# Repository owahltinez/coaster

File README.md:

# Coaster

Very simple battery-operated device. When you push a button, the light turns on for a few seconds
and then it turns off. It is designed to be used as a coaster such that, when gently pushing a glass
down on the device, the light activates making the contents of the glass glow.

Pressing down on the coaster triggers a ~8 second light show: the LEDs ramp up to full
brightness, "breathe" gently five times, and fade back to black. Between shows the device
sleeps at ~1 µA — there is no on/off switch and none is needed.

## Repository layout

- `firmware/` — AVR C firmware and its build/flash Makefile.
- `pcb/` — v0.3 board design (KiCad, generated from python scripts) and footprints.
- `enclosure/` — 3D-printed shell (FreeCAD source + STEP/STL export).
- `tools/` — pinned toolchain containers (KiCad for the board, avr-gcc for the firmware).

All subdirectories share the same verbs, and the top-level Makefile forwards to each:
`make build` (firmware hex + board + enclosure exports), `make test` (flash-fit check +
board DRC + enclosure solidity check), `make clean`. Domain-specific verbs forward to the
relevant subdirectory: `make flash` / `make fuses` (firmware programming),
`make review` (board render / PDF / STEP), `make fab` (JLCPCB order bundle). The
firmware and PCB verbs run inside pinned containers — `make image` builds them once
(see Software); flashing stays on the host.

## How it works

The button connects an MCU pin (with its internal pull-up) to ground. Pressing it fires a
falling-edge interrupt on one of the ATtiny202's fully-asynchronous pins, which wakes the
chip from power-down sleep with the main clock stopped — a press costs effectively no
charge. The firmware debounces the edge, plays the show over hardware PWM through a
MOSFET driving four series-resistored LEDs, and goes back to sleep.

Two details carry hard-won lessons from v0.2:

- The show also plays once when the battery is inserted (a power-on reset doubles as a
  built-in self test), but *only* on a power-on reset: a brown-out reset means a dying
  cell sagged below 1.8V mid-show, and playing again would loop the cell to death — so a
  brown-out goes straight back to sleep and the coaster simply dims gracefully as the
  battery wears out.
- Wake edges that turn out not to be presses (e.g. contact bounce while lifting a glass
  off a held-down button) are filtered by a 20ms debounce check, so the show plays on
  deliberate presses only.

## Hardware

The v0.3 design (KiCad) lives in `pcb/`:

- `pcb/design.py` is the circuit as data — parts, placements, and the netlist defined
  once. This is the file to read or edit; it is the source of truth.
- `pcb/DESIGN.md` is the design specification: pin map, BOM with part rationale,
  ordering plan, and the validation checklists.
- `pcb/generate.py` turns `design.py` into `coaster.kicad_pcb` (committed for
  convenience). `make build` regenerates the board and validates connectivity; `make
  test` runs DRC; `make review` produces a board render, a 1:1 printable PDF, and a STEP
  model for CAD fit checks.
- `pcb/coaster.pretty/` — project footprints with pad geometry extracted from the
  manufactured v0.2 board (battery holder, tactile switch).

There is no schematic: JLCPCB takes Gerbers + BOM + CPL (not a schematic), the board is
built and checked directly against `design.py`, and `design.py` itself documents the
circuit — so a derived schematic would add nothing.

The previous revision (v0.2: ATtiny13A, EasyEDA, CR2032) is archived at release
[v0.2.1](https://github.com/owahltinez/coaster/releases/tag/v0.2.1), including its
firmware, schematic renderings, and 3D printing assets.

### Production

All SMD parts are LCSC-stocked, so the board can be fabricated and assembled through
JLCPCB — the only hand-assembly per unit is dropping a CR2016 into the holder. `make
fab` writes the three JLCPCB uploads (Gerbers zip + BOM + CPL) to `pcb/dist/`; order
with **white soldermask** (the board face is the reflector behind the LEDs). The full
step-by-step — orientation checks, stock confirmation, post-assembly flashing — is the
ordering plan in [pcb/DESIGN.md](pcb/DESIGN.md).

Rough per-unit estimates as of June 2026 (USD, assembled and shipped; ~A$1.55/US$):

| Per unit               | Qty 30  | Qty 100 | Qty 1k  | Qty 10k |
|------------------------|---------|---------|---------|---------|
| Parts                  | $0.74   | $0.70   | ~$0.60  | ~$0.47  |
| Feeder/setup/stencil   | $0.72   | $0.30   | ~$0.04  | ~$0     |
| PCB + assembly         | $0.47   | $0.40   | ~$0.30  | ~$0.20  |
| Board shipping         | $0.20   | $0.35   | ~$0.10  | ~$0.05  |
| CR2016 (name-brand)    | $0.65   | $0.35   | ~$0.20  | ~$0.12  |
| Enclosure              | $0.60 (FDM) | $0.60 (FDM) | ~$1.00 (print farm)\* | ~$0.30 (molded)\* |
| **Finished coaster**   | **~$3.40** | **~$2.70** | **~$2.25** | **~$1.10** |

\*The 1k column keeps FDM but prices it honestly: ~2,500 printer-hours, which a small
farm of four budget printers clears in under a month — filament plus printer
amortization lands near $1/unit, with no tooling commitment and the printers kept at
the end. The 10k column switches to injection molding (aluminum tooling, amortized);
that is also the column where a further redesign pays — shrinking the PCB from the
structural 50×50mm to a ~25mm puck and letting the molded shell carry the mechanical
roles would cut the PCB line by ~$0.10 more. If 1k is a milestone toward 10k rather
than the destination, rapid aluminum tooling (~$1–1.5k) prices similarly at 1k and
carries forward.

The electronics architecture is the same in every column — the MCU ($0.30–0.43) is the
cheapest line that matters, and it is the entire personality of the product. Prices
drift; get a real quote from the [JLCPCB quote tool](https://jlcpcb.com/quote) and
confirm ATtiny202 stock at order time (the ATtiny402 is a firmware-compatible drop-in
substitute).

## Software

The firmware and board builds run in **pinned containers** (`tools/`), so the host
needs neither a KiCad nor an AVR toolchain — only a container engine. Pinning is what
keeps the artifacts reproducible: the committed board is KiCad-10 format and host KiCad
drifts (Debian ships v9, which can't even open a v10 board), and the ATtiny202 firmware
needs avr-gcc ≥ 12 (the README used to hand-source `avr-gcc@14` from the
[osx-cross/avr](https://github.com/osx-cross/homebrew-avr) tap on macOS). Build the
images once, then the verbs route through them automatically:

```bash
make image               # build both images: coaster-fw + coaster-pcb (re-run after editing a Containerfile)
make build               # firmware hex + board + enclosure, each in its toolchain
make fab                 # regenerate the board + emit the JLCPCB bundle, in the container
```

The enclosure builds the same way, in a pinned FreeCAD 1.1.1 container (`make image`
builds it too) — so the host needs no FreeCAD either, and the old macOS `freecadcmd`
symlink dance is gone.

`docker` here is a [Podman](https://podman.io) alias (`podman-docker`); override
`CONTAINER_ENGINE` to use another runtime. Rootless Podman maps container-root to your
UID (the Makefile passes `--user 0`), so generated files come back owned by you. The
rule is **produce artifacts in a container, touch hardware on the host** — so flashing
(`make flash` / `make fuses`, which need a USB-serial adapter) stays on the host and
needs `avrdude` (≥ 7, for `serialupdi`) installed there; see Flashing below.

The **enclosure** build still runs on the host via FreeCAD (`freecadcmd`); on macOS the
app bundle doesn't expose its CLI, so symlink it once:

```bash
ln -s /Applications/FreeCAD.app/Contents/Resources/bin/freecadcmd /opt/homebrew/bin/freecadcmd
```

### Flashing

No dedicated programmer needed: UPDI works over any USB-serial adapter with a single
~1kΩ resistor bridging the adapter's TX to RX, and RX wired to the board's UPDI pad
(plus VDD and GND — the J1 pads are labeled on the silkscreen).

```bash
make flash   # writes main.hex over serialupdi
make fuses   # once per chip: brown-out detector at 1.8V, sampled in sleep
```

The fuses matter: the factory default leaves the BOD disabled, which allows undefined
behavior when the battery sags, and the firmware's brown-out logic depends on it.

For flashing a stack of boards hands-free, `make flash-loop` runs a continuous loop:
plug a board onto the jig, it flashes + fuses + verifies automatically, then waits for
you to remove it before arming the next. **The board reports its own result** — a good
flash plays a distinct rapid blink and a failed one stays dark, so you never look at the
screen. The blink is gated on a one-shot EEPROM flag the loop writes only after both
flash and fuses verify (a single avrdude run, which aborts before the arm step on any
earlier failure); the firmware blinks once on the next boot and clears the flag, so it
fires exactly once per flash and never again in the field.

Gotchas:

- **Remove the coin cell before flashing.** The adapter drives VDD and would back-feed
  the (non-rechargeable) lithium cell.
- That's it. The v0.2 list of ISP gotchas (LEDs clamping MOSI, flaky readback, wedged
  programmers) died with the ISP header: UPDI shares no pins with anything else on this
  board, by construction.

## Power estimates

Assumptions: CR2016 rated at 75 mAh (~70 mAh usable), ~8 mA LED draw at 100% duty on a
fresh cell, ~1 µA sleep current (BOD sampled).

| Event                  | Cost     | Notes                                          |
|------------------------|----------|------------------------------------------------|
| Light show (~8 s)      | ~15 µAh  | avg ~60% LED duty + ~1.5 mA MCU active         |
| Button press           | ~0       | pin-change wake; nothing touches the supply    |
| Standby (per day)      | ~26 µAh  | ~1 µA sleep + battery self-discharge           |

Expected battery life:

| Usage pattern               | Battery life      |
|-----------------------------|-------------------|
| Never pressed (shelf)       | ~7 years          |
| ~5 presses/day              | ~2 years          |
| ~30 presses/day (bar duty)  | ~5 months         |
| Theoretical max shows       | ~4,500            |

The punchline: v0.3 runs on a cell with a third of the v0.2 battery's capacity and
still matches its life, because presses are now free (each v0.2 press dead-shorted the
battery and cost as much as a show) and sleep current dropped ~4×.

## Demo

> TODO: Add demo pictures / video.

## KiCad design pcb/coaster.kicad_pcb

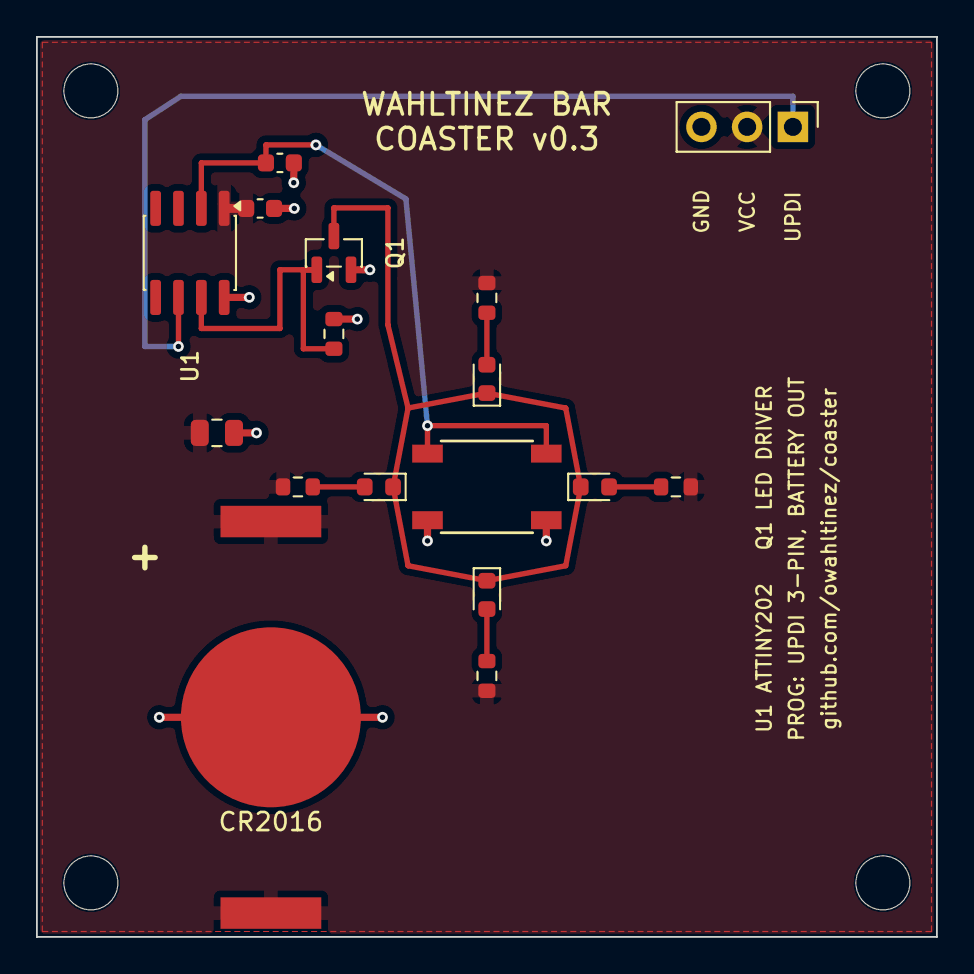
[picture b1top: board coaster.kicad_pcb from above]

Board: 2 copper layers, 50.0 x 50.0 mm, 21 parts (0 on the bottom side), 10 nets.

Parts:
BT1: CR2016; MY-2016-02
C1, C3: 100nF; C_0603_1608Metric
C2: 22uF; C_0805_2012Metric
H1, H2, H3, H4: 3mm; MountingHole_3mm
J1: UPDI; PinHeader_1x03_P2.54mm_Vertical
L1, L2, L3, L4: KT-0603W; LED_0603_1608Metric
Q1: AO3400A; SOT-23
R1, R2, R3, R4: 100; R_0603_1608Metric
R5: 100k; R_0603_1608Metric
SW1: TS-1187A-B-A-B; TS-1187A
U1: ATtiny202-SSN; SOIC-8_3.9x4.9mm_P1.27mm

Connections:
BUTTON: C3.1, SW1.1, U1.2
GND: BT1.2, C1.2, C2.2, C3.2, J1.3, Q1.2, R5.2, SW1.2, U1.8
LED_A1: L1.2, R1.2
LED_A2: L2.2, R2.2
LED_A3: L3.2, R3.2
LED_A4: L4.2, R4.2
LED_K: L1.1, L2.1, L3.1, L4.1, Q1.3
LED_PWM: Q1.1, R5.1, U1.7
UPDI: J1.1, U1.6
VCC: BT1.1, C1.1, C2.1, J1.2, R1.1, R2.1, R3.1, R4.1, U1.1

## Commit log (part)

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2024-06-26 Update BOM with SMD parts
2024-08-01 Pulse LED using PWM
2024-08-17 Simplify LED routine
2026-06-06 Make flashing reliable over a hand-held ISP cable
    Fix the install target (usbasp uses -P usb, no baud rate; drop -F)
    and tune it for this board's quirks: the LEDs hang on the MOSI line,
    so writes silently truncate at higher ISP clocks while reads stay
    reliable (data returns on the unloaded MISO line). Write at 32kHz
    without inline verification, then verify in a separate pass at
    16kHz. Add a fuses target for the one-time BOD setup and a reset
2026-06-06 Fix reset-relight loop and add breathing glow effect
    A worn CR2032 sagging under LED load could brown out the MCU
    mid-show; since a reboot unconditionally replayed the show, the
    device got stuck relighting forever. Three layers of fixes:
    - Enable BOD at 1.8V awake (requires hfuse=0xFD) so low-voltage
    operation resets cleanly instead of executing undefined behavior,
    and disable it during sleep via BODCR (the BODS bits are not in
2026-06-06 Document hardware: design files, BOM, flashing, power estimates
    Add the design files (Protel netlist as the canonical machine-readable
    circuit description, schematic SVG for humans, EasyEDA source for
    editing) and rewrite the README: how the device works, flashing
    recipe with fuse settings and hard-won gotchas, BOM matching the SMD
    parts actually on the board (with verified sources and pricing),
    JLCPCB production cost estimates, power budget and battery life
2026-06-08 Add v0.3 KiCad hardware design, generated and verified
    Reorganize the repo into three domain folders, each with a
    self-contained Makefile, plus a top-level Makefile that forwards to
    them (make install / board / review / clean):
    firmware/ AVR C firmware and its build/flash Makefile
    pcb/ v0.3 board design + generator + footprints
    enclosure/ 3D-printed shell (design constraints; CAD source TODO)
2026-06-09 Fix long-press brown-out and simplify show-on-press logic
    Two related fixes to the wake-and-play behavior, both rooted in the
    v0.2 button dead-shorting the battery to power-cycle the MCU:
    - Replace the .noinit SRAM cookie with the MCUSR PORF reset flag to
    decide whether to play the show. The cookie distinguished a button
    press from a mid-show brown-out by whether SRAM survived, which is
    timing-dependent and differed between short and long presses --
2026-06-09 Make board regeneration deterministic
    Every KiCad board item gets a random UUID at construction and KiCad
    serializes items in UUID order, so each generate.py run rewrote every
    UUID and reshuffled the file -- a ~4000-line no-op diff on regeneration.
    Seed KiCad's UUID generator (pcbnew.KIID.SeedGenerator) with a fixed
    value before building; with the script's fixed build order this makes
    the UUID sequence, and thus the whole file, byte-stable across runs.
2026-06-09 Switch battery to CR2016 (MY-2016-02) to slim the enclosure
    The battery holder was the tallest component, sitting just above the
    button. Swap the CR2032 holder (MY-2032-12, 3.6mm tall) for a CR2016
    holder (MY-2016-02, 2.2mm) -- 1.4mm lower. ~75mAh still gives 2+ years
    at a few presses a day, since µA sleep dominates and presses are ~free.
    New footprint land pattern is from the MY-2016-02 datasheet (WD-CP-0081):
    clip pads 5.6x1.75mm at 21.75mm center-to-center, 10mm center contact --
2026-06-11 Add v0.2.1 enclosure CAD source with STEP/STL export build
    The FreeCAD source of truth for the 3D-printed shell: Top (spiral
    flexure lid), Bottom (PCB tray), and Shield (thin insert between PCB
    and lid) bodies. export.py runs under freecadcmd to validate the
    document (full recompute, every body a valid closed solid) and export
    per-body STEP and STL files; the enclosure Makefile exposes the same
    build/test/clean verbs as firmware/ and pcb/, and the top-level
2026-06-11 Make board and enclosure builds work on macOS
    KiCad and FreeCAD app bundles don't expose their CLIs on PATH, so the
    README now documents one-time symlinks for kicad-cli, freecadcmd, and
    kicad-python (KiCad's bundled interpreter, the one with the pcbnew
    bindings). The Makefiles call the commands by name; the only lookup
    left is the pcb build preferring kicad-python over python3, and
    generate.py resolving the stock footprint library path per platform.
2026-06-11 Swap Q1 to AO3400A for logic-level gate drive
    The 2N7002's gate threshold is spec'd up to 2.5V worst-case, which a
    CR2016 spends most of its life barely above -- a high-threshold part
    plus a worn cell reads as dim or flickering LEDs. The AO3400A (LCSC
    C20917, JLCPCB basic catalog, same SOT-23 pinout and price) is fully
    enhanced at 2.5V with Vgs(th) of 0.65-1.45V.
2026-06-11 Move battery-return vias out of the cell contact pad
    The CR2016 presses directly on BT1 pad 2 (bare copper, mask-defined),
    and the two GND stitching vias sat inside that 10mm contact circle --
    drill dimples and flux right at the contact surface risk an
    intermittent battery connection that presents as random resets. The
    vias now sit just outside the circle, fed by short spokes from the pad
    center.
2026-06-11 Keep SW1 as TS-1187A, record the rationale
    The enclosure flexure is dimensioned around this switch's body height
    and actuation force, and its footprint is the one extracted from the
    manufactured v0.2 board. The basic-catalog alternative would save
    ~$0.10/board at qty 30 against the cost of re-validating press feel.
2026-06-11 Document the shield as the liquid strategy
    The Shield body is a continuous clear-PETG membrane over the PCB:
    drips through the flexure's spiral cuts land on it and shed outward
    instead of reaching the electronics, the bare battery contact, or the
    switch. Record the planned center-post retention groove (the current
    snap-fit holds by hoop tension, which creep relaxes and every press
    flexes) and add a splash test to the first-article checklist.
2026-06-11 Add LED brightness validation to the first-article checklist
    v0.2 brightness was set by battery sag; v0.3's is set by R1-R4, so the
    two won't match by construction. 150R is a starting value to verify
    through an actual glass, with 100R as the rework fallback.
2026-06-11 Upgrade LEDs to XL-1608UWC-04 for ~3x brightness at the same current
    Same 0603 footprint and 120 degree viewing angle as the KT-0603W, but
    400 min / 630 typ mcd at 20mA versus 173-207. Cool white, Vf 2.6-2.8V
    typical, LCSC C965808 (JLCPCB extended: one more $3 feeder fee, or
    $0.10/board at qty 30). Also note white soldermask in the ordering
    plan -- the board face is the reflector behind the LEDs under the
    clear shield.
2026-06-11 Record enclosure material use: ~29g of filament per coaster
    Sliced at 0.20mm / 0.4 nozzle / 15% infill: Top 8.8 cm3 (~11g PLA),
    Bottom 10.7 cm3 (~13g PLA), Shield 3.7 cm3 (~4.6g PETG). A measured
    3-coaster print (74g for three Top+Bottom pairs) agrees within 2%.
2026-06-11 Swap U1 to the ATtiny202 to cut the dominant BOM cost
    Same SOIC-8 pinout, peripherals, sleep current, and firmware as the
    ATtiny402 -- only flash/SRAM shrink (2KB/128B, still 7x the current
    firmware) -- for $0.43 vs $0.65 (LCSC C2052951). The 402 stays a
    drop-in substitute at order time: a binary built for the 202 runs on
    it unmodified.
2026-06-11 Port firmware to the ATtiny202
    The v0.2 firmware existed to work around the v0.2 board: PWM as the
    only LED current limit, PORF forensics to tell presses from brown-outs,
    and a settle phase to let the cell recover from the wake dead-short.
    The v0.3 board removes the causes, so the port is mostly deletion:
    - Wake: PA6 falling-edge interrupt from power-down (fully-async pin);
    a 20ms debounce also filters release-bounce edges so lifting a glass
2026-06-11 Rewrite README for v0.3
    The BOM, power table, flashing recipe, and how-it-works narrative all
    described the v0.2 board (ATtiny13A, CR2032, dead-short wake, usbasp
    gotchas), which is archived at release v0.2.1. Describe v0.3 instead:
    GPIO wake with the brown-out fail-dark logic, UPDI flashing over a
    USB-serial adapter, updated cost and battery-life estimates, and a
    pointer to pcb/DESIGN.md for the BOM instead of a second copy that
2026-06-11 Add economies-of-scale table to the production estimates
    Per-unit cost at qty 30 / 100 / 1k / 10k, separating the lines that
    amortize (fees, fixed costs, battery, enclosure process) from the ones
    that don't (parts). The same design lands at ~$3.40 in a hobby batch,
    ~$2.25 at 1k with a small FDM print farm (no tooling commitment, with
    rapid aluminum tooling as the alternative when 1k is a milestone
    toward 10k), and ~$1.10 at 10k with a molded shell -- the gap is
2026-06-12 Automate the JLCPCB bundle and run the toolchain in pinned containers
    Two related changes that make the board orderable and the whole build
    reproducible off any host.
    Order automation:
    - pcb/fab.py + `make fab` emit the three JLCPCB uploads (Gerbers zip, BOM,
    CPL) from the board geometry and design.py's part data.
    - design.py gains the LCSC numbers, assembly exclusions (J1 header, mounting
2026-06-14 Add a calibrated axisymmetric press simulation for the donut-piston Top
    Slices the FreeCAD solid through its axis, meshes the meridian (Gmsh, CAX6),
    and solves the press in CalculiX — the geometry is read from the model, never
    reconstructed, so the simulation cannot drift from the CAD. Calibrated from one
    measured click force and cross-validated against a second press at a different
    radius; emits a click-force-vs-load-radius curve plus a validation table.
    Runs via `make sim` in the pinned FreeCAD container (gmsh and ccx ship in the
2026-06-16 Swap LEDs to KT-0603W and drop LED resistors to 100Ω
    The v0.3 board specified XL-1608UWC-04 LEDs (C965808) on the stated
    rationale that they were ~3x brighter than the basic KT-0603W. The
    datasheet says otherwise: XL-1608UWC-04 is 130mcd@20mA, KT-0603W is
    360mcd@5mA. At the few mA a CR2016 drives through these LEDs, the
    KT-0603W is ~11x brighter at the operating point — and it's a Basic
    part, so no feeder fee. Drop R1-R4 150Ω→100Ω to push a little more
2026-06-16 Sync enclosure to the v0.3 donut-piston Top (drop the shield)
    The committed enclosure was still the v0.2.1 spiral-flexure design — three
    bodies including a clear-PETG Shield. The v0.3 enclosure (authored in Drive as
    Coaster v0.2.2.FCStd) is a solid donut-piston: the top is a continuous skin
    that deflects as a whole, on a ring of snap arms, with no spiral cuts. Verified
    the Top is built entirely from additive pads (zero pockets/cuts) and its top
    face is a full continuous disc — so there is no open liquid path, and the
2026-06-26 Thin the v0.3 enclosure 1mm and rework the snap arms
    - BottomHeight 7.5->6.5mm (8.1mm assembled); press post shortened
    4.5->3.5mm so the post tip stays on the button
    - Snap arms: outer root fillet 0.4->0.8mm and flexing beam thinned
    1.75->1.0mm to cut root bending strain
    - Snap pockets tightened to 0.1mm tangential clearance (was 0.2)
    - sim: meridian arm-detection made geometry-relative so it tracks a
